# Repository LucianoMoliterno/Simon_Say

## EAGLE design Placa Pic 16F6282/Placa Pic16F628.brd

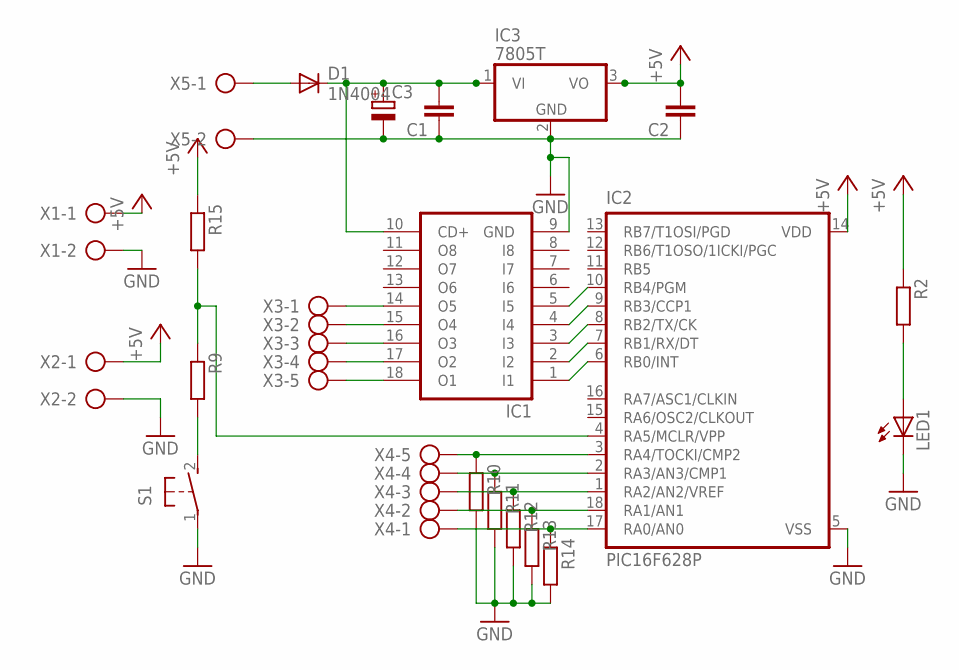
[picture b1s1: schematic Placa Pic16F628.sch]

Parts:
C1, C2: C-EU050-030X075; C050-030X075
C3: CPOL-EUB45181B; B45181B
D1: 1N4004; DO41-10
IC1: ULN2803A; DIL18
IC2: PIC16F628P; DIL18
IC3: 7805T; TO220H
LED1: LED5MM
R2, R9, R10, R11, R12, R13, R14, R15: R-EU_0207_12; 0207/12
S1: 31-XX; B3F-31XX
X1, X2, X5: AK300/2
X3, X4: AK300/5

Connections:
+5V: C2.2, IC2.14 (VDD), IC3.3 (VO), R2.1, R15.1, X1.1, X2.1
GND: C1.1, C2.1, C3.-, IC1.9 (GND), IC2.5 (VSS), IC3.2 (GND), LED1.K (C), R10.2, R11.2, R12.2, R13.2, R14.2, S1.1, X1.2, X2.2, X5.2
unnamed: IC1.1 (I1), IC2.6 (RB0/INT)
unnamed: IC1.2 (I2), IC2.7 (RB1/RX/DT)
unnamed: IC1.3 (I3), IC2.8 (RB2/TX/CK)
unnamed: IC1.4 (I4), IC2.9 (RB3/CCP1)
unnamed: IC1.5 (I5), IC2.10 (RB4/PGM)
unnamed: IC2.3 (RA4/TOCKI/CMP2), R10.1, X4.5
unnamed: IC2.2 (RA3/AN3/CMP1), R11.1, X4.4
unnamed: IC2.1 (RA2/AN2/VREF), R12.1, X4.3
unnamed: IC2.18 (RA1/AN1), R13.1, X4.2
unnamed: LED1.A, R2.2
unnamed: D1.A, X5.1
unnamed: IC2.4 (RA5/MCLR/VPP), R9.1, R15.2
unnamed: R9.2, S1.2 (S)
unnamed: IC2.17 (RA0/AN0), R14.1, X4.1
unnamed: C1.2, C3.+, D1.C, IC1.10 (CD+), IC3.1 (VI)
unnamed: IC1.14 (O5), X3.1
unnamed: IC1.15 (O4), X3.2
unnamed: IC1.16 (O3), X3.3
unnamed: IC1.17 (O2), X3.4
unnamed: IC1.18 (O1), X3.5

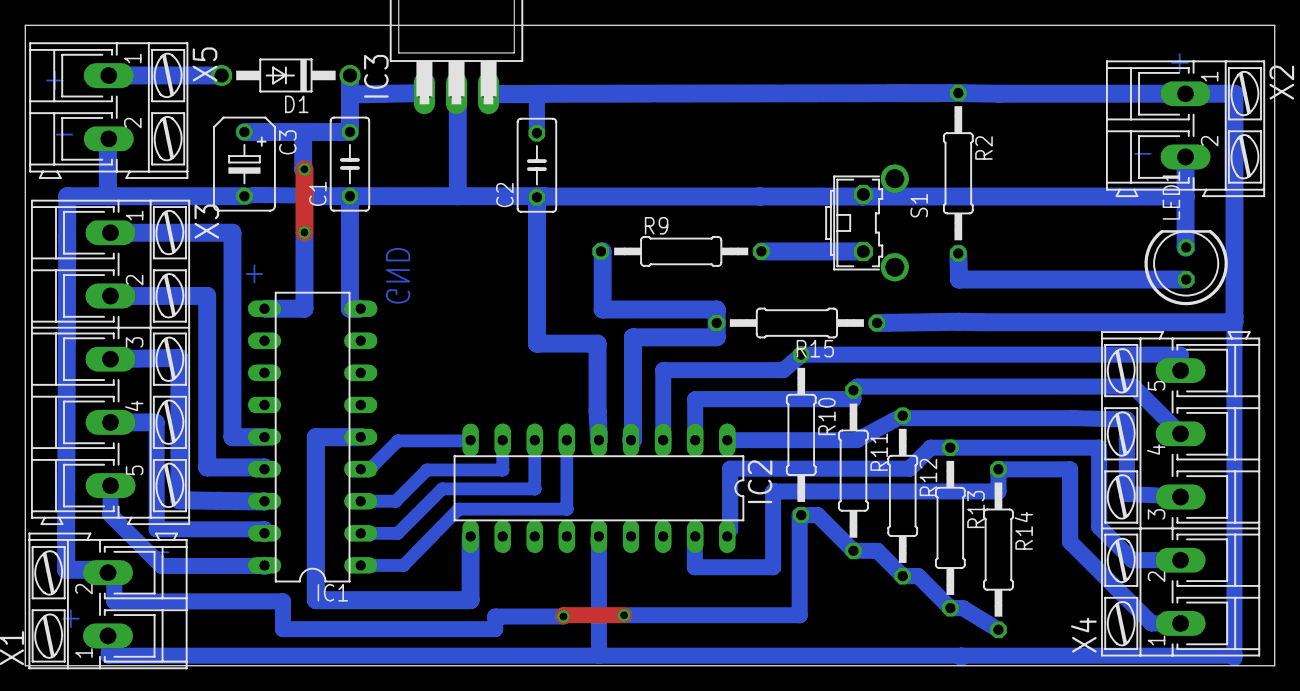
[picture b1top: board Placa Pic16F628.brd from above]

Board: 2 copper layers, 98.9 x 50.7 mm, 22 parts (0 on the bottom side), 22 nets.

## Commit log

2023-05-18 Game Simon Says
